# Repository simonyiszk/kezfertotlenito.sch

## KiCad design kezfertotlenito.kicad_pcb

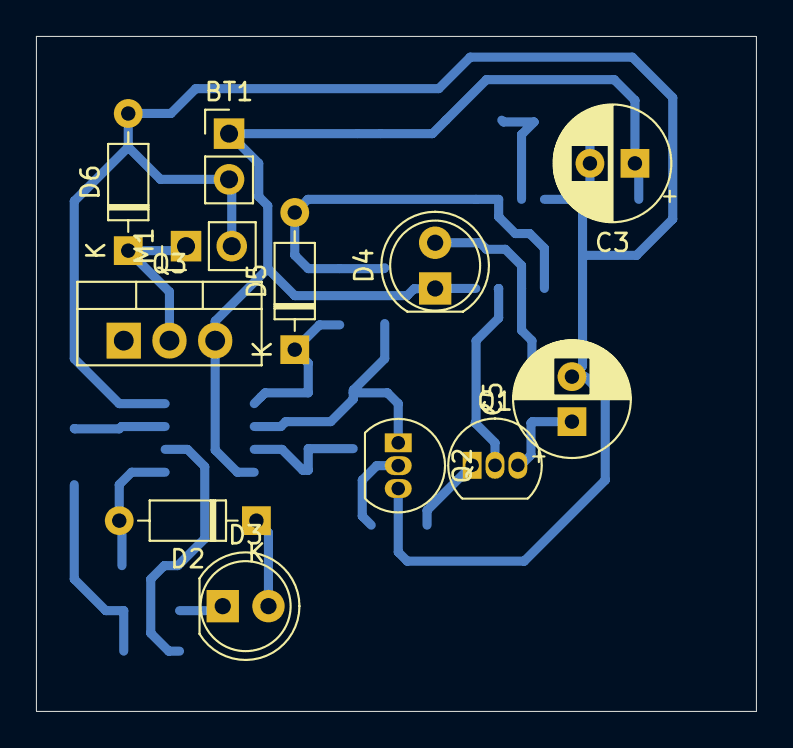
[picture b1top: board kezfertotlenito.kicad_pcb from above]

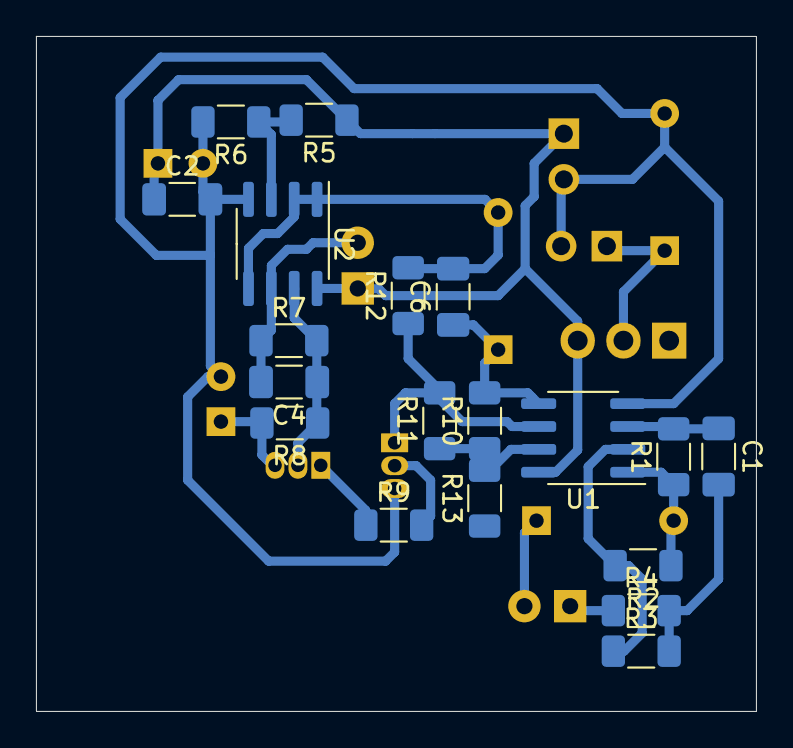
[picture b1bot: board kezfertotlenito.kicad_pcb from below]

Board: 2 copper layers, 40.0 x 37.5 mm, 31 parts (19 on the bottom side), 19 nets.

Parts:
BT1: 12V; PinHeader_1x02_P2.54mm_Vertical
C1, C4: 470n; C_1206_3216Metric_Pad1.33x1.80mm_HandSolder
C2: 100n; C_1206_3216Metric_Pad1.33x1.80mm_HandSolder
C3: 47u; CP_Radial_D6.3mm_P2.50mm
C5: 4u7; CP_Radial_D6.3mm_P2.50mm
C6: 750n; C_1206_3216Metric_Pad1.33x1.80mm_HandSolder
D2, D5: BAT42; D_DO-35_SOD27_P7.62mm_Horizontal
D3: LED; LED_D5.0mm
D4: D_Photo; LED_D5.0mm
D6: 1N4148; D_DO-35_SOD27_P7.62mm_Horizontal
M1: A1150; PinHeader_1x02_P2.54mm_Vertical
Q1: BC556; TO-92_Inline
Q2: BC547; TO-92_Inline
Q3: IRF9540N; TO-220-3_Vertical
R1, R10: 1M; R_1206_3216Metric_Pad1.30x1.75mm_HandSolder
R2, R3, R11, R12: 300k; R_1206_3216Metric_Pad1.30x1.75mm_HandSolder
R4: 270; R_1206_3216Metric_Pad1.30x1.75mm_HandSolder
R5, R6: 600k; R_1206_3216Metric_Pad1.30x1.75mm_HandSolder
R7: 40k; R_1206_3216Metric_Pad1.30x1.75mm_HandSolder
R8: 200k; R_1206_3216Metric_Pad1.30x1.75mm_HandSolder
R9: 400k; R_1206_3216Metric_Pad1.30x1.75mm_HandSolder
R13: 0; R_1206_3216Metric_Pad1.30x1.75mm_HandSolder
U1, U2: TLC2252; SOIC-8_3.9x4.9mm_P1.27mm

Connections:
+6V: BT1.1, C2.1, C3.1, D4.1, Q3.3, R5.1, U1.8, U2.8
-6V: BT1.2, C2.2, C3.2, C5.2, D6.2, M1.2, Q2.3, R6.2, U1.4, U2.4
GND: C1.2, C6.2, D5.2, R3.2, R4.2, R12.2, U2.1, U2.2, U2.5
unnamed: C1.1, R1.2, U1.3
unnamed: C4.1, Q1.2, R7.2, R8.1, U2.7
unnamed: C4.2, D4.2, R7.1, U2.6
unnamed: C5.1, Q1.3, R8.2
unnamed: C6.1, D5.1, R10.2, U1.5
unnamed: D2.1, D3.2
unnamed: D2.2, R1.1, R2.1, U1.1
unnamed: D3.1, R4.1
unnamed: D6.1, M1.1, Q3.2
unnamed: Q1.1, R9.1
unnamed: Q2.1, R11.2, R12.1, U1.6
unnamed: Q2.2, R9.2
unnamed: Q3.1, R13.1
unnamed: R2.2, R3.1, U1.2
unnamed: R5.2, R6.1, U2.3
unnamed: R10.1, R11.1, R13.2, U1.7

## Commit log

2020-10-12 Kezdő commit
2020-10-12 Proto NYÁK
